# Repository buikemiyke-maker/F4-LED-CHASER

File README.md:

# F4-LED-CHASER
I created this LED Chaser as a kind of side project to see much more Ive improved.

# BOM
1× NE555P (DIP-8), 1× CD4017BE (DIP-16), 10× 5 mm LEDs (D1–D10), 1× 1 kΩ resistor (R1), 1× 470 Ω resistor (R2), 1× 50 kΩ potentiometer (RV1), 1× 0.01 µF ceramic capacitor (C1), 1× 1 µF electrolytic capacitor (C2), 2× M3 mounting holes (H1, H2).

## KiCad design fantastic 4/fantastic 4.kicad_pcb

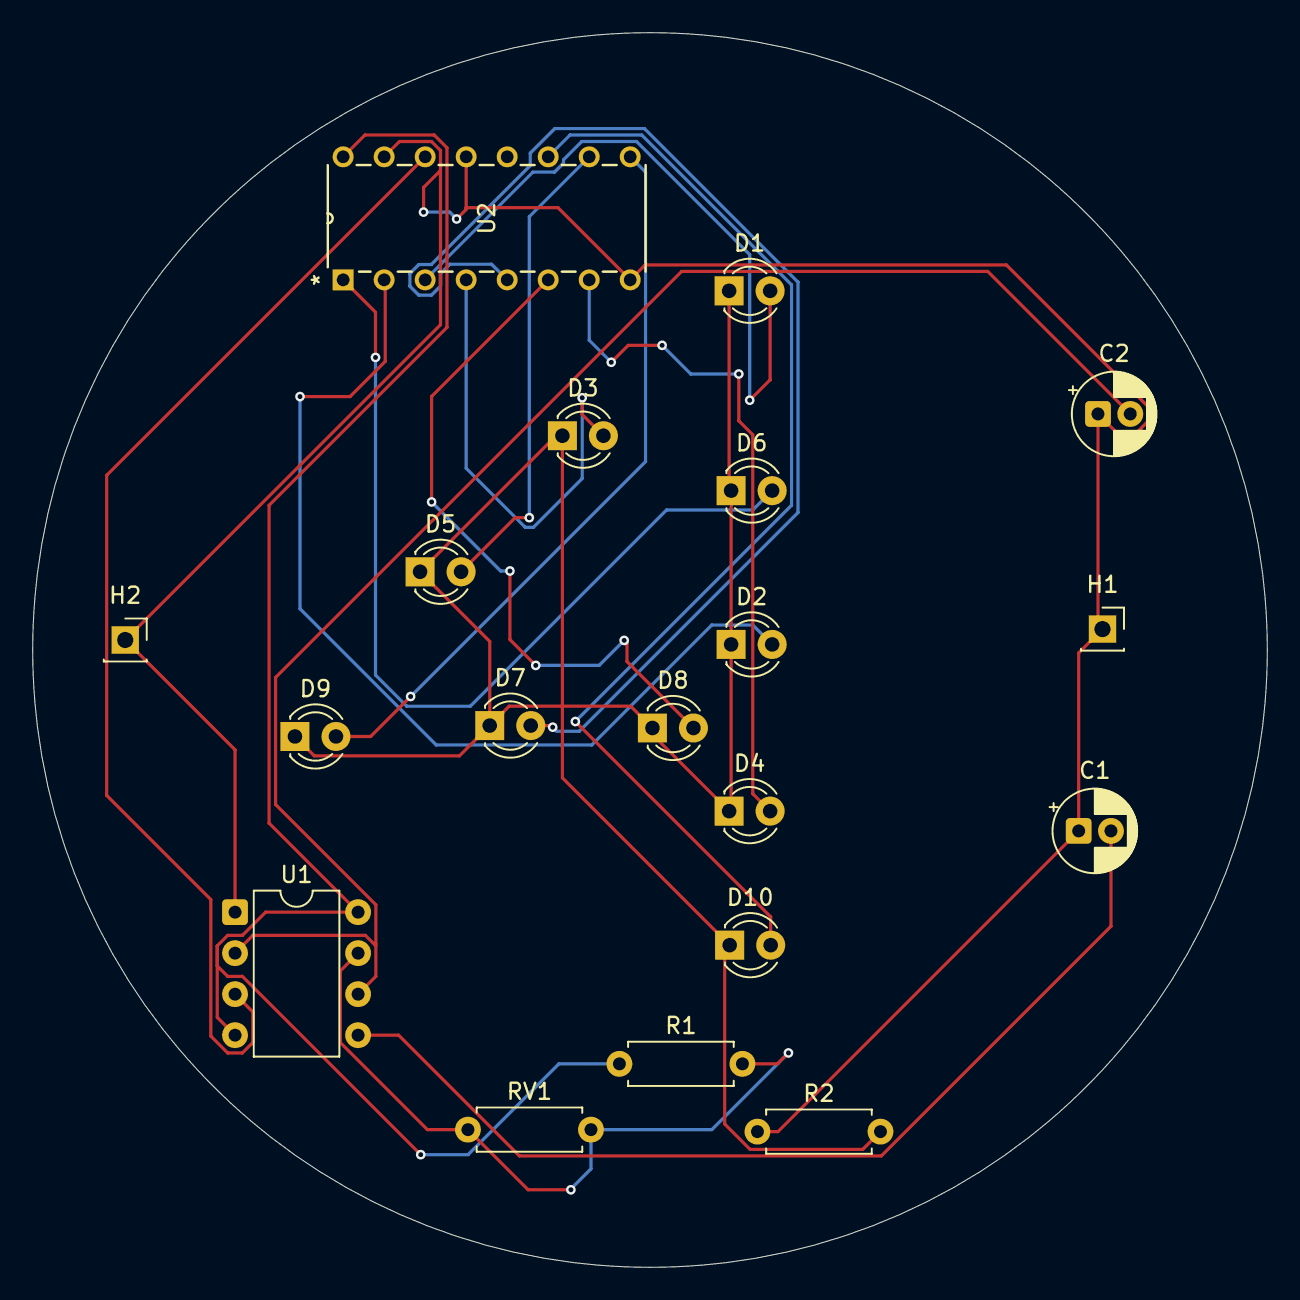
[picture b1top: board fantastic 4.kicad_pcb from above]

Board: 2 copper layers, 76.5 x 76.5 mm, 19 parts (0 on the bottom side), 17 nets.

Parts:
C1: 0.01 uF; CP_Radial_D5.0mm_P2.00mm
C2: 1 uF; CP_Radial_D5.0mm_P2.00mm
D1, D2, D3, D4, D5, D6, D7, D8, D9, D10: LED; LED_D3.0mm
H1, H2: MountingHole_Pad; PinSocket_1x01_P2.54mm_Vertical
R1: 1K; R_Axial_DIN0207_L6.3mm_D2.5mm_P7.62mm_Horizontal
R2: 470; R_Axial_DIN0207_L6.3mm_D2.5mm_P7.62mm_Horizontal
RV1: 50k; R_Axial_DIN0207_L6.3mm_D2.5mm_P7.62mm_Horizontal
U1: NE555P; DIP-8_W7.62mm
U2: 4017; N16

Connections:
+5V: R1.1, U1.4 (R), U1.8 (VCC), U2.16 (VDD)
GND: C1.1, C2.1, H1.1, H2.1, R2.1, U1.1 (GND), U2.8 (VSS), U2.13 (CKEN), U2.15 (Reset)
unnamed: D1.2 (A), U2.3 (Q0)
unnamed: D1.1 (K), D2.1 (K), D3.1 (K), D4.1 (K), D5.1 (K), D6.1 (K), D7.1 (K), D8.1 (K), D9.1 (K), D10.1 (K), R2.2
unnamed: D2.2 (A), U2.2 (Q1)
unnamed: D3.2 (A), U2.4 (Q2)
unnamed: D4.2 (A), U2.7 (Q3)
unnamed: D5.2 (A), U2.10 (Q4)
unnamed: D6.2 (A), U2.1 (Q5)
unnamed: D7.2 (A), U2.5 (Q6)
unnamed: D8.2 (A), U2.6 (Q7)
unnamed: D9.2 (A), U2.9 (Q8)
unnamed: D10.2 (A), U2.11 (Q9)
unnamed: C1.2, U1.5 (CV)
unnamed: R1.2, RV1.1, RV1.2, U1.7 (DIS)
OUT: U1.3 (Q), U2.14 (CLK)
TR: C2.2, U1.2 (TR), U1.6 (THR)
